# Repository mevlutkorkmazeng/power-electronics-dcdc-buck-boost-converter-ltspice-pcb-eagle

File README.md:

# Power Electronics Project: DC-DC Buck and Boost Converter (LTspice)

This project focuses on the design and simulation of DC-DC power converters using LTspice.
The main objective is to understand the operating principles of **Buck (step-down)** and **Boost (step-up)** converters and analyze their electrical behavior through simulation.

In this project, a Buck converter circuit is designed and simulated to observe switching behavior, current waveforms, and output voltage characteristics.

---

## Project Overview

This project demonstrates the design and simulation of a **DC-DC Buck Converter** using LTspice.
The converter steps down a **12V input voltage** to a lower output voltage using PWM switching control.

Key features analyzed in this project:

* PWM switching behavior
* Inductor current waveform
* Output voltage ripple
* Basic converter performance

---

## Project Goals

* Understand how DC-DC converters work
* Design a Buck converter circuit
* Design a Boost converter circuit
* Simulate the circuits in LTspice
* Observe voltage and current waveforms
* Analyze output voltage ripple
* Study switching behavior in power electronic converters

---

## Buck Converter Circuit

The circuit consists of a MOSFET switching device, a diode, an inductor, a capacitor, and a resistive load.
The MOSFET is driven by a PWM signal that controls the duty cycle and therefore regulates the output voltage.

---

## Converter Specifications

| Parameter           | Value   |
| ------------------- | ------- |
| Input Voltage       | 12 V    |
| Inductor            | 100 µH  |
| Capacitor           | 100 µF  |
| Load Resistance     | 10 Ω    |
| Switching Frequency | 2.5 kHz |
| Duty Cycle          | ~35%    |

---

## Buck Converter Simulation Results

### PWM Gate Signal and Output Voltage

This waveform shows the PWM gate signal applied to the MOSFET and the resulting output voltage of the Buck converter.

The duty cycle of the PWM signal determines the average output voltage according to the basic Buck converter relationship.

---

### Inductor Current

The inductor current waveform has a triangular shape which is characteristic of Buck converters operating in continuous conduction mode.

During the ON state, the inductor stores energy.
During the OFF state, the inductor releases energy to the load through the diode.

---

### Output Voltage Ripple

The output voltage ripple appears due to the switching operation of the converter.
The LC filter reduces the ripple and provides a more stable DC output voltage.

---

## Simulation Analysis

The simulation confirms the expected behavior of a Buck converter:

* The output voltage is lower than the input voltage due to duty cycle control.
* The inductor current follows a triangular waveform.
* The capacitor reduces voltage ripple at the output.
* PWM switching controls the energy transfer from input to load.

These results demonstrate the fundamental operating principles of DC-DC power converters.

---

## Buck Converter Operating Principle

A Buck converter is a DC-DC step-down converter that reduces the input voltage to a lower output voltage using high-frequency switching.

The converter operates in two main switching states:

**Switch ON State**

* The MOSFET conducts.
* The inductor stores energy.
* Current increases through the inductor.
* The load receives energy from the input source.

**Switch OFF State**

* The MOSFET turns OFF.
* The diode conducts.
* The inductor releases stored energy to the load.
* The capacitor helps maintain a smooth output voltage.

By controlling the **PWM duty cycle**, the average output voltage of the converter can be regulated.

---
## PCB Design

After completing the simulation phase, the Buck Converter circuit was implemented as a printed circuit board (PCB) using Autodesk EAGLE.

The PCB design includes:
- IRLZ44Z power MOSFET
- 1N4004 freewheeling diode
- 100 µH inductor
- 100 µF output capacitor
- 10 Ω load resistor

A ground plane was added to improve current return paths and reduce noise in the switching converter.

### PCB Layout

---
## Project Structure

* `docs/` → theory notes and design explanations
* `simulations/` → LTspice simulation files
* `results/` → simulation analysis and observations
* `pcb/` → PCB preparation notes
* `images/` → simulation screenshots used in the README

---

## Tools Used

* LTspice
* Power Electronics design principles
* Basic circuit analysis
* GitHub for project documentation

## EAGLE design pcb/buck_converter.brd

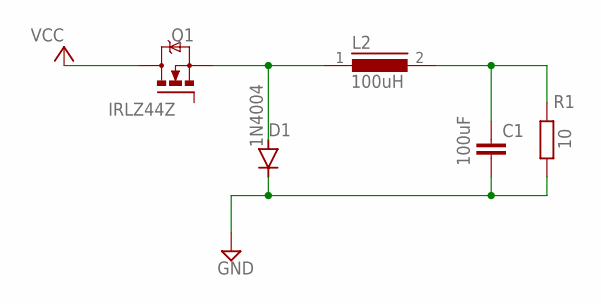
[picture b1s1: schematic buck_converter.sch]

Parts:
C1: 100uF; C7.5B3
D1: 1N4004; DO41-10
L2: 100uH; 82114R
Q1: IRLZ44Z; TO220BH
R1: 10; R0805

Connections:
GND: C1.2, D1.C, R1.1
unnamed: D1.A, L2.1, Q1.S
unnamed: C1.1, L2.2, R1.2
VCC: Q1.D

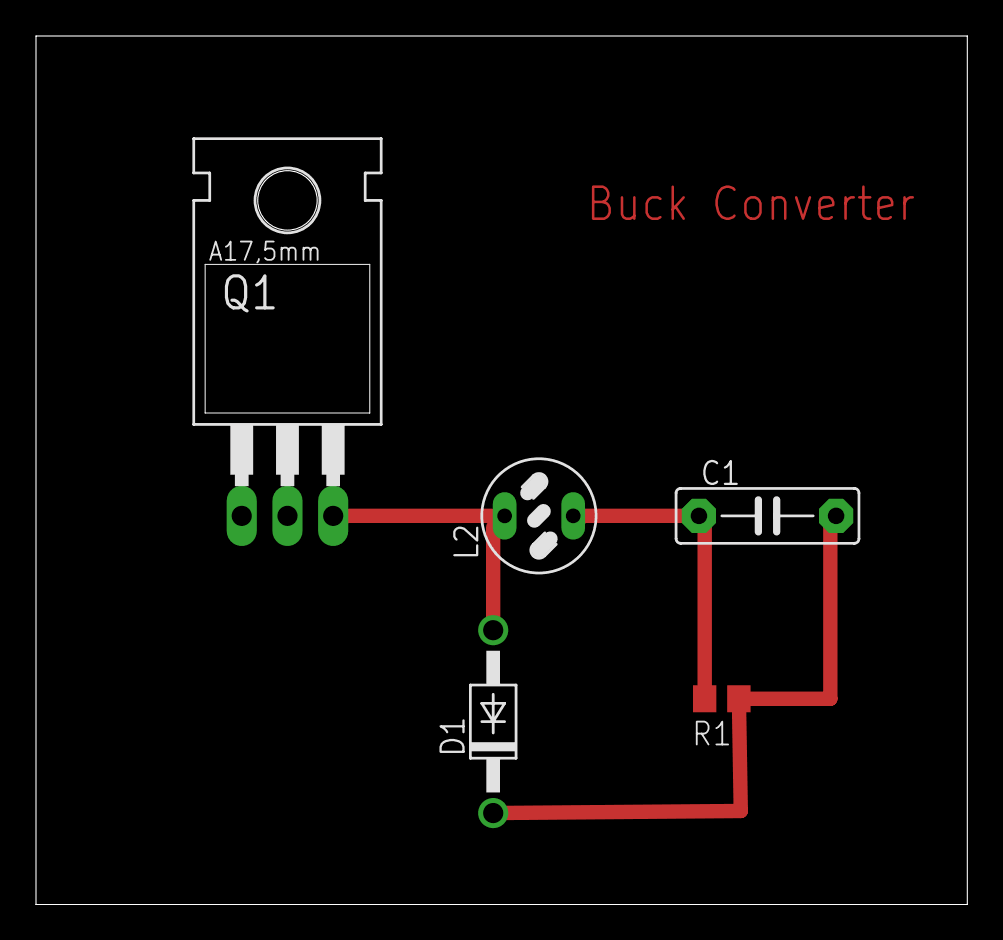
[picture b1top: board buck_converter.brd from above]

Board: 2 copper layers, 51.7 x 48.2 mm, 5 parts (0 on the bottom side), 3 nets.

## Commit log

2026-03-06 Create simulations folder and add notes
2026-03-06 Create pcb folder and add design notes
2026-03-06 Create results folder and add notes
2026-03-06 Add initial buck converter simulation plan
2026-03-06 Add initial buck converter design notes
2026-03-06 remove placeholder file
2026-03-06 rewrite README with simulation results
2026-03-06 update pwm and output waveform image
2026-03-06 add converter specifications
2026-03-06 add simulation analysis
2026-03-06 improve project scope description
2026-03-06 Add Buck Converter PCB design and Gerber files
2026-03-06 Add PCB design section
